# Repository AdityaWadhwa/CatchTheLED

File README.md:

# CatchTheLED
MSP430 based game to test hand eye coordination.

This project is a simple game developed using the Texas Instruments Microcontroller Unit, the MSP430.

‘Catch the LED’ is a fun manifestation to test the concentration ability of a person. It assists the person to increase ones focus and make the reflexes better. In this game we have to press the switch whenever the reference colour appears on any of the other 3 RGB led’s , hence the name.

 We basically aim to develop a MSP430 based project which generates random numbers using PSEUDO RANDOM NUMBER GENERATOR. The random numbers were then linked to the different colours of the led and the aim of the game is to “catch” a particular colour on the reference led using a switch.
 
The project was developed under the guidance of Mr. D.V Gadre, CEDT lab in Netaji Subhas Institute of Technology (now, Netaji Subhas University of Technology).

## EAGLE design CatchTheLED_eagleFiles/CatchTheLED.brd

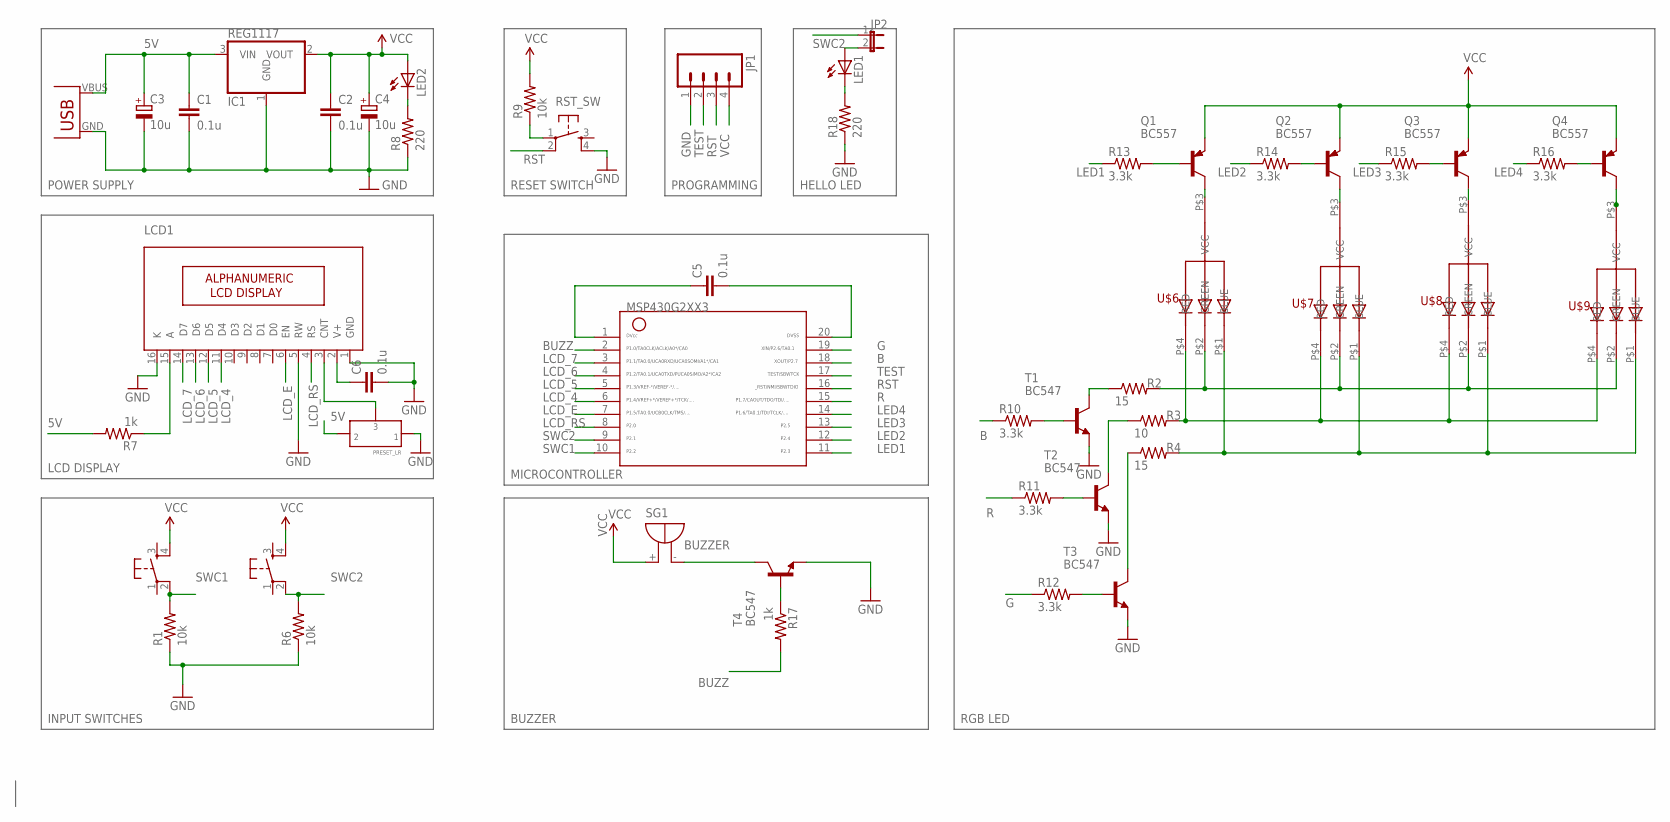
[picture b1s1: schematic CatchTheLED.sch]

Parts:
C1, C2, C5, C6: 0.1u; C025-025X050
C3, C4: 10u; E2,5-5
IC1: REG1117; SOT223
JP1: M04; 04P
JP2: JP1E; JP1
LCD1: 16X2LCD; 16X2_LCD
LED1, LED2: LED3MM
Q1, Q2, Q3, Q4: BC557; TO92
R1, R6, R9: 10k; 0207/7
R2, R4: 15; 0207/7
R3: 10; 0207/7
R7, R17: 1k; 0207/7
R8, R18: 220; 0207/7
R10, R11, R12, R13, R14, R15, R16: 3.3k; 0207/7
RST_SW: OMRON_SWITCH_10-XX; B3F-10XX
SG1: BUZZER; F/TMB
T1, T2, T3, T4: BC547; TO92
U$1: USB(POWER)
U$2: MSP430G2553DIP20; G2553-DIP20
U$3, U$4: OMRON_SWITCH_40-XX; B3F-40XX
U$5: PRESET_LR
U$6, U$7, U$8, U$9: 5MMRGBLED; LED5MMRGB

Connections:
5V: C1.1, C3.+, C6.1, IC1.3 (VIN), LCD1.2 (V+), R7.2, U$1.VBUS (VCC), U$5.P$2 (2)
B: R10.1, U$2.18
BUZZ: R17.2, U$2.2
G: R12.1, U$2.19
GND: C1.2, C2.2, C3.-, C4.-, C5.2, C6.2, IC1.1 (GND), JP1.1, LCD1.1 (GND), LCD1.5 (RW), LCD1.16 (K), R1.1, R6.1, R8.1, R18.1, RST_SW.4 (S1), T1.1 (E), T2.1 (E), T3.1 (E), T4.1 (E), U$1.GND, U$2.20, U$5.P$1 (1)
LCD_4: LCD1.11 (D4), U$2.6
LCD_5: LCD1.12 (D5), U$2.5
LCD_6: LCD1.13 (D6), U$2.4
LCD_7: LCD1.14 (D7), U$2.3
LCD_E: LCD1.6 (EN), U$2.7
LCD_RS: LCD1.4 (RS), U$2.8
LED1: R13.1, U$2.11
LED2: R14.1, U$2.12
LED3: R15.1, U$2.13
LED4: R16.1, U$2.14
unnamed: R10.2, T1.2 (B)
unnamed: R2.2, U$6.P$2 (GREEN), U$7.P$2 (GREEN), U$8.P$2 (GREEN), U$9.P$2 (GREEN)
unnamed: R3.2, U$6.P$4 (RED), U$7.P$4 (RED), U$8.P$4 (RED), U$9.P$4 (RED)
unnamed: R4.2, U$6.P$1 (BLUE), U$7.P$1 (BLUE), U$8.P$1 (BLUE), U$9.P$1 (BLUE)
unnamed: SG1.-, T4.3 (C)
unnamed: Q1.3 (C), U$6.P$3 (VCC)
unnamed: Q2.3 (C), U$7.P$3 (VCC)
unnamed: JP2.2, LED1.A
unnamed: R3.1, T2.3 (C)
unnamed: Q3.3 (C), U$8.P$3 (VCC)
unnamed: LED2.K (C), R8.2
unnamed: R9.1, RST_SW.1
unnamed: Q4.3 (C), U$9.P$3 (VCC)
unnamed: LCD1.3 (CNT), U$5.P$3 (3)
unnamed: LCD1.15 (A), R7.1
unnamed: R11.2, T2.2 (B)
unnamed: R12.2, T3.2 (B)
unnamed: R2.1, T1.3 (C)
unnamed: R4.1, T3.3 (C)
unnamed: Q1.2 (B), R13.2
unnamed: Q2.2 (B), R14.2
unnamed: Q3.2 (B), R15.2
unnamed: Q4.2 (B), R16.2
unnamed: R17.1, T4.2 (B)
unnamed: LED1.K (C), R18.2
R: R11.1, U$2.15
RST: JP1.3, RST_SW.2 (P1), U$2.16
SWC1: R1.2, U$2.10, U$3.2 (P1)
SWC2: JP2.1, R6.2, U$2.9, U$4.2 (P1)
TEST: JP1.2, U$2.17
VCC: C2.1, C4.+, C5.1, IC1.2 (VOUT), JP1.4, LED2.A, Q1.1 (E), Q2.1 (E), Q3.1 (E), Q4.1 (E), R9.2, SG1.+, U$2.1, U$3.4 (S1), U$4.4 (S1)

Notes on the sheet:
INPUT SWITCHES
LCD DISPLAY
POWER SUPPLY
RESET SWITCH
PROGRAMMING
HELLO LED
BUZZER
RGB LED
MICROCONTROLLER

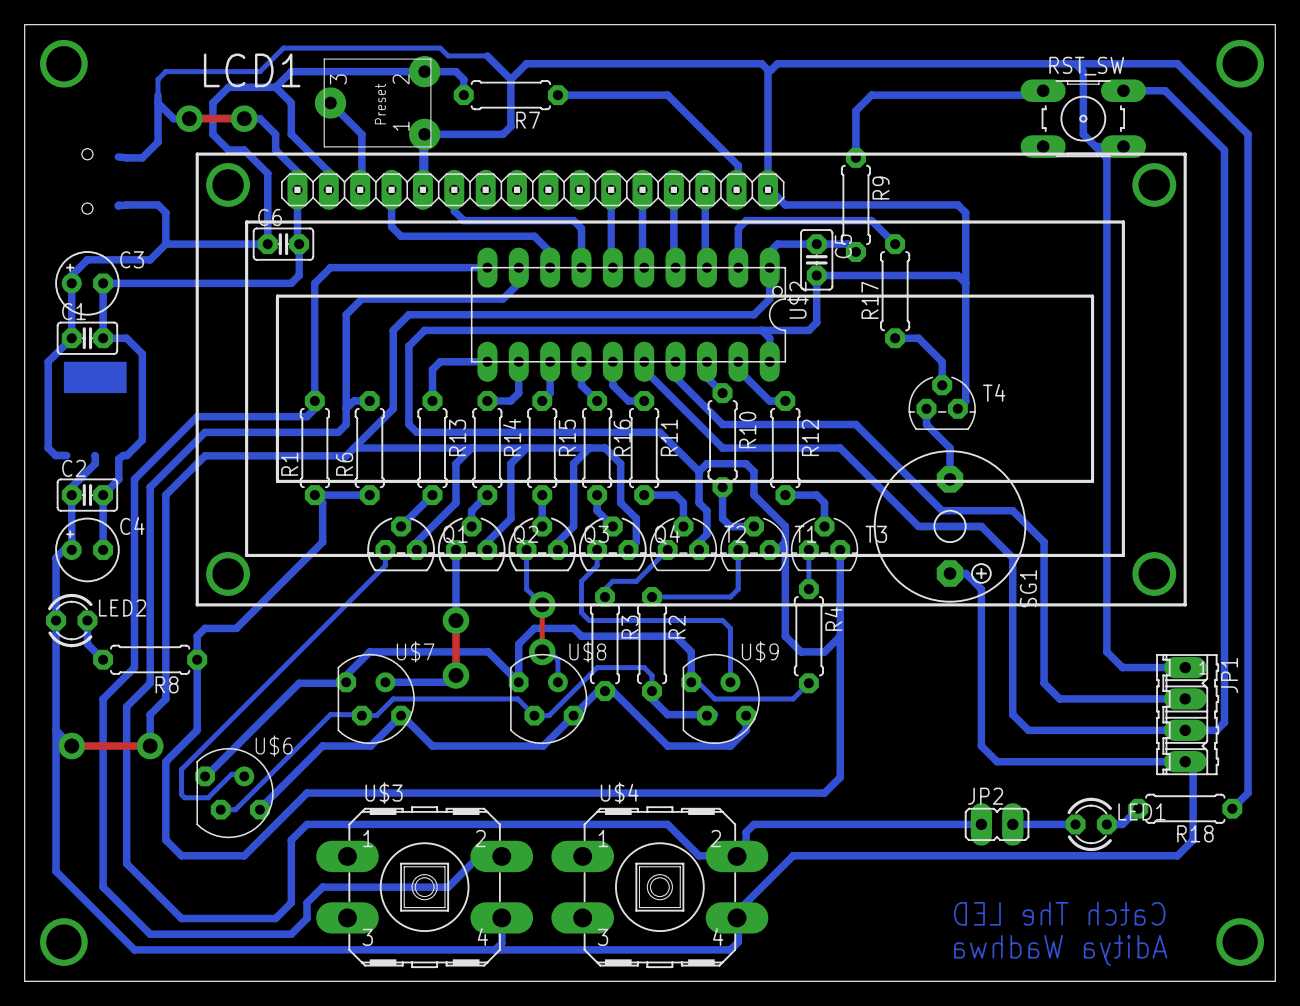
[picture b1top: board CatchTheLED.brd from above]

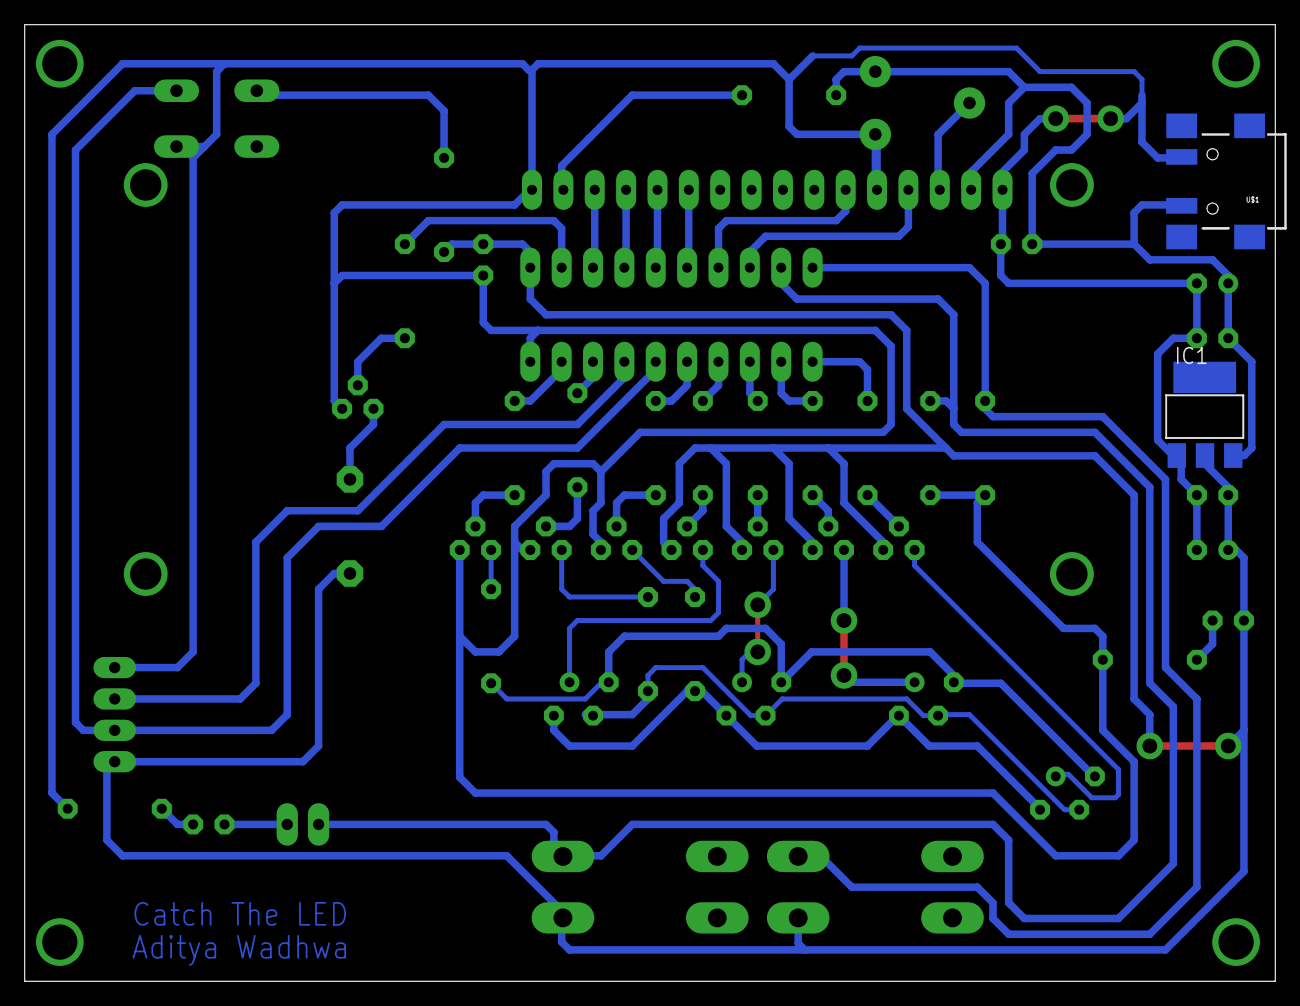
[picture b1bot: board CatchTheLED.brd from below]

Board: 2 copper layers, 101.3 x 77.5 mm, 48 parts (2 on the bottom side), 46 nets.

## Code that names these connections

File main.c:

#include <msp430.h>
#include <inttypes.h>
#include <lcd.h>
#include "rand.h"


#define CMD         0
#define DATA        1

#define LCD_OUT     P1OUT
#define LCD_DIR     P1DIR
#define D4          BIT4
#define D5          BIT3
#define D6          BIT2
#define D7          BIT1
#define RS          BIT0
#define EN          BIT5

#define R       BIT7
#define G       BIT7
#define B       BIT6
#define LED1    BIT3
#define LED2    BIT4
#define LED3    BIT5
#define LED4    BIT6

#define SW1     BIT2
#define SW2     BIT1
#define BUZZ    BIT0
/**
 * Random number generator.
 *
 * It is recommended that this function is run during setup, before any clocks
 * or timers have been set and before interrupts have been enabled. While it
 * does restore all used control registers to their original values, it also
 * expects that nothing interesting will happen when it modifies them.
 *
 * Algorithm from TI SLAA338:
 * http://www.ti.com/sc/docs/psheets/abstract/apps/slaa338.htm
 *
 * @return 16 random bits generated from a hardware source.
 */

volatile int a,b,c,d,k,m;
volatile int score=5;

unsigned int rand(void) {
    int i, j;
    unsigned int result = 0;

    /* Save state */
    unsigned int BCSCTL3_old = BCSCTL3;
    unsigned int TACCTL0_old = TACCTL0;
    unsigned int TACTL_old = TACTL;

    /* Halt timer */
    TACTL = 0x0;

    /* Set up timer */
    BCSCTL3 = (~LFXT1S_3 & BCSCTL3) | LFXT1S_2; // Source ACLK from VLO
    TACCTL0 = CAP | CM_1 | CCIS_1;            // Capture mode, positive edge
    TACTL = TASSEL_2 | MC_2;                  // SMCLK, continuous up

    /* Generate bits */
    for (i = 0; i < 16; i++) {
        unsigned int ones = 0;

        for (j = 0; j < 5; j++) {
            while (!(CCIFG & TACCTL0));       // Wait for interrupt

            TACCTL0 &= ~CCIFG;                // Clear interrupt

            if (1 & TACCR0)                   // If LSb set, count it
                ones++;
        }

        result >>= 1;                         // Save previous bits

        if (ones >= 3)                        // Best out of 5
            result |= 0x8000;                 // Set MSb
    }

    /* Restore state */
    BCSCTL3 = BCSCTL3_old;
    TACCTL0 = TACCTL0_old;
    TACTL = TACTL_old;

    return result;
}

/**
 * Pseudo-random number generator.
 *
 * Implemented by a 16-bit linear congruential generator.
 * NOTE: Only treat the MSB of the return value as random.
 *
 * @param state Previous state of the generator.
 * @return Next state of the generator.
 */
/*unsigned int prand(unsigned int state) {
    return M * state + I;                     // Generate the next state of the LCG
}*/



color(int i,int j)
{
    P1OUT &= ~R;
    P1OUT |= LED4;
    P2OUT |= (LED1 + LED2 + LED3);
    P2OUT &= ~(G+B);

    if(j==1)
    {
        P2OUT &= ~LED1;
    }
    else if(j==2)
    {
        P2OUT &= ~LED2;
    }
    else if(j==3)
    {
        P2OUT &= ~LED3;
    }
    else if(j==4)
    {
        P1OUT &= ~LED4;
    }


    if(i==1)
    {
        P1OUT |= R;
    }
    else if(i==2)
    {
        P2OUT |= G;
    }
    else if(i==3)
    {
        P2OUT |= B;
    }
    else if(i==4)
    {
        P1OUT |= R;
        P2OUT |= G;
    }
    else if(i==5)
    {
        P2OUT |= G;
        P2OUT |= B;
    }
    else if(i==6)
    {
        P1OUT |= R;
        P2OUT |= B;
    }
}

void lcd(void)
{
    lcd_setCursor(0,1);

    switch(a)
    {
    case 1:
        lcd_print(" CATCH THE RED ");
        break;

    case 2:
        lcd_print(" CATCH THE GREEN ");
        break;

    case 3:
        lcd_print(" CATCH THE BLUE ");
        break;

    case 4:
        lcd_print(" CATCH THE YELLOW ");
        break;

    case 5:
        lcd_print(" CATCH THE CYAN ");
        break;

    case 6:
        lcd_print(" CATCH THE PINK ");
        break;


    }

    lcd_setCursor(1,0);
    lcd_print("    SCORE :    ");
    lcd_setCursor(1,12);
    lcd_write((char)(score+48),1);
}

void cleanUp()
{
    P1OUT &= ~R;
    P1OUT |= LED4;
    P2OUT |= (LED1 + LED2 + LED3);
    P2OUT &= ~(G+B);

}


void main(void)
{
    WDTCTL = WDTPW + WDTHOLD; // stop watchdog
    __enable_interrupt();
    lcd_init(P1, D4, D5, D6, D7, P2, RS, P1, EN);
    lcd_setCursor(0,0);
    lcd_print("   WELCOME TO   ");
    lcd_setCursor(1,1);
    lcd_print(" CATCH THE LED ");

    P1DIR|=BUZZ;
    P1OUT&=~BUZZ;

    P2DIR&=~SW1;
    P2IE|=SW1;
    P2IFG&=~SW1;
    P2IES|=SW1;
    P2SEL &= ~(BIT6+BIT7);      //set 2.6 and 2.7 as GPIO pin
    P1DIR |= (R+LED4);
    P2DIR |= (LED1 + LED2 + LED3+G+B);

    a=rand()%6+1;
    __delay_cycles(5000000);
    lcd();

    while(1)
    {
        //a=rand()%6 + 1;

        if(score<0||score>9)
            break;

        for(k=0;k<20;k++)
        {
            b=rand()%6 + 1;
            c=rand()%6 + 1;
            d=rand()%6 + 1;
            for(m=0;m<200;m++)
            {
                color(a,1);
                __delay_cycles(250);
                color(b,2);
                __delay_cycles(250);
                color(c,3);
                __delay_cycles(250);
                color(d,4);
                __delay_cycles(250);
            }
        }
        __delay_cycles(50000);

    }
}

#pragma vector=PORT2_VECTOR;
    __interrupt void abc(void)
    {
           if((a==b)||(a==c)||(a==d))
           {
               score++;
               if(score>9)
               {
                      lcd_setCursor(0,0);
                      lcd_print("    YOU WON     ");
                      cleanUp();
                      exit(0);
               }

           }
           else
           {
               score--;
               P1OUT|=BUZZ;
               __delay_cycles(100000);
               P1OUT&=~BUZZ;
               __delay_cycles(100000);
               P1OUT|=BUZZ;
               __delay_cycles(100000);
               P1OUT&=~BUZZ;

               if(score<0)
               {
                     lcd_setCursor(0,0);
                     lcd_print("    YOU LOST    ");
                     cleanUp();
                     exit(0);
               }

           }

           //lcd_init(P1, D4, D5, D6, D7, P2, RS, P1, EN);
           /*lcd_setCursor(0,0);
           lcd_write(LCD_CLEARDISPLAY, CMD);                   // Clear screen
           delay(20);
           lcd_setCursor(1,0);
           lcd_write(LCD_CLEARDISPLAY, CMD);                   // Clear screen
           delay(20);*/

           lcd_setCursor(1,12);
           lcd_write((char)(score+48),1);


           for(m=0;m<2000;m++)
                       {
                           color(a,1);
                           __delay_cycles(250);
                           color(b,2);
                           __delay_cycles(250);
                           color(c,3);
                           __delay_cycles(250);
                           color(d,4);
                           __delay_cycles(250);
                       }

           a=rand()%6+1;

           lcd();

           P2IFG&=~SW1;
    }
